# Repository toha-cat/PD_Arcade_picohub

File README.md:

# PD Arcade picohub
=================================

Firmware for Raspberry Pi Pico for use in Hatsune Miku Project DIVA Arcade Future Tone DIY-arcade controller 

Creates two USB-CDC and one HID devices:
- UART-bridge for connection [LKP](https://github.com/Project-Alpaca/LKP)-slider with [LKP-Serial](https://github.com/Project-Alpaca/LKP-FW) firmware.
- virtual COM-port that receives the commands for controlling the LEDs. Works in conjunction with the [PD-Arcade-Lights plugin](https://github.com/steelpuxnastik/PD-Arcade-Lights)
- HID-Gamepad for 5 buttons.

Example of PCB and it's description in [PCB folder](/PCB)

## Raspberry Pi Pico pin mapping
------------------------

| Raspberry Pi Pico GPIO | Function |
|-------------|-------------|
| 			**[LKP](https://github.com/Project-Alpaca/LKP)-slider connection**				|
| GPIO16 (Pin 21)        | UART0 TX |
| GPIO17 (Pin 22)        | UART0 RX |
| **LEDs**      |
| GPIO2 (Pin 4)          | BTN4  LED (Circle) |
| GPIO3 (Pin 5)          | BTN3  LED (Cross) |
| GPIO4 (Pin 6)          | BTN2  LED (Square) |
| GPIO5 (Pin 7)          | BTN1  LED (Triangle) |
| GPIO6 (Pin 9)          | R LINE B (RGB LED strip)|
| GPIO7 (Pin 10)         | R LINE R (RGB LED strip)|
| GPIO8 (Pin 11)         | R LINE G (RGB LED strip)|
| GPIO9 (Pin 12)         | L LINE B (RGB LED strip)|
| GPIO10 (Pin 14)        | L LINE R (RGB LED strip)|
| GPIO11 (Pin 15)        | L LINE G (RGB LED strip)|
| GPIO15 (Pin 20)        | LED-strip brightness PWM signal source|
| **Controls**	 			|
| GPIO18 (Pin 24)        |  BTN 1  (Triangle) |
| GPIO19 (Pin 25)        |  BTN 2  (Square) |
| GPIO20 (Pin 26)        |  BTN 3  (Cross) |
| GPIO21 (Pin 27)        |  BTN 4  (Circle) |
| GPIO22 (Pin 29)        |  BTN 5 (Start)  |

## Disclaimer
----------

This software is provided without warranty, according to the MIT License, and should therefore not be used where it may endanger life, financial stakes, or cause discomfort and inconvenience to others.

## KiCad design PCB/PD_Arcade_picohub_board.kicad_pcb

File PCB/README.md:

# PD Arcade picohub PCB
=================================

## Parts list
- PCB: 1x `PD_Arcade_picohub_board` **1.6mm thickness** (KiCad 7.99+ (7.99.0-697-g4d05bd62da), release build required for exporting Gerber files or take Gerber files archive in `PCB/gerber/PD_Arcade_picohub_board.zip`)
  - U1: `Raspberry Pi Pico` board
  - U2, U3: 2x `ULN2003` transistor assembly
  - U4: `TXS0108EPW` bi-directional level-shifter *(used for connection [SHINSANWASWITCH](https://github.com/steelpuxnastik/SHINSANWASWITCH) optical switches as main buttons and [LKP](https://github.com/Project-Alpaca/LKP) slider. Those components are basically uses 5v power supply, that is why it needs level shifter to connect to Raspberry Pi Pico that uses 3.3v signal level. There are possible other configurations of those components and in case of their 3.3v power supply you can exclude `TXS0108EPW` and connect them directly to Raspberry Pi Pico pins bypassing level shifter)*
  - C1, C2: `0.1uf` 0603 SMD condenser *(used for level shifter)*
- Parts for PWM brightness control (short jumpers if no PWM used, **brightness control will not work**):
  - Q1: `IRFR9024N` P-channel MOSFET
  - Q2: `AO3404A` N-channel MOSFET
  - R1: `1k` 1206 SMD resistor
  - R2: `10k` 1206 SMD resistor
- connectors:
  - 2x DIP-16 panel for `ULN2003`
  - 5x `JST XH-02` male connector
  - 4x `JST XH-03` male connector *(used for connection [SHINSANWASWITCH](https://github.com/steelpuxnastik/SHINSANWASWITCH) optical switches for main buttons. It's an active component, so it uses 3 wires. If you use passive switches - you can change to `JST XH-02` and connect it directly to Raspberry Pi Pico pins bypassing level shifter)*
  - 6x `JST XH-04` male connector
  - female 2.54 single row headset for `Raspberry Pi Pico`

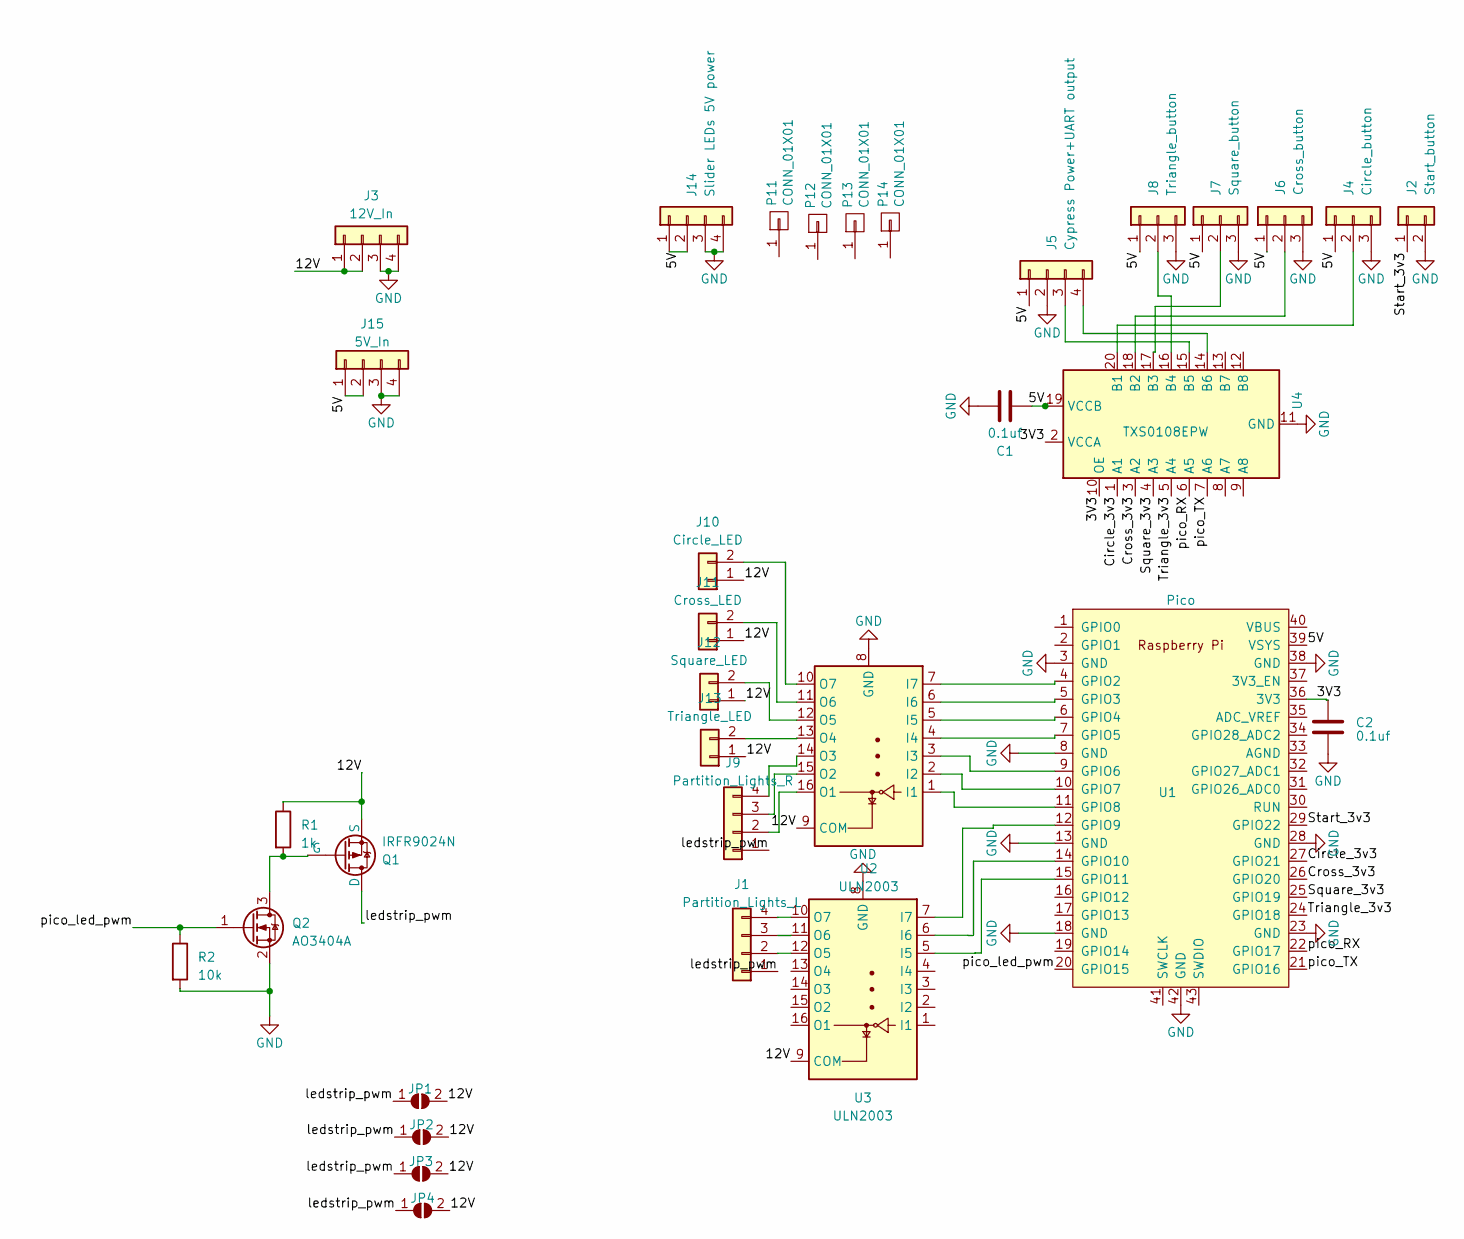
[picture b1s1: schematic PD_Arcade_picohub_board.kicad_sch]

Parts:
C1, C2: 0.1uf; C_0805_2012Metric
J1: Partition_Lights_L; JST_XH_B4B-XH-A_1x04_P2.50mm_Vertical
J2: Start_button; JST_XH_B2B-XH-A_1x02_P2.50mm_Vertical
J3: 12V_In; JST_XH_B4B-XH-A_1x04_P2.50mm_Vertical
J4: Circle_button; JST_XH_B3B-XH-A_1x03_P2.50mm_Vertical
J5: Cypress Power+UART output; JST_XH_B4B-XH-A_1x04_P2.50mm_Vertical
J6: Cross_button; JST_XH_B3B-XH-A_1x03_P2.50mm_Vertical
J7: Square_button; JST_XH_B3B-XH-A_1x03_P2.50mm_Vertical
J8: Triangle_button; JST_XH_B3B-XH-A_1x03_P2.50mm_Vertical
J9: Partition_Lights_R; JST_XH_B4B-XH-A_1x04_P2.50mm_Vertical
J10: Circle_LED; JST_XH_B2B-XH-A_1x02_P2.50mm_Vertical
J11: Cross_LED; JST_XH_B2B-XH-A_1x02_P2.50mm_Vertical
J12: Square_LED; JST_XH_B2B-XH-A_1x02_P2.50mm_Vertical
J13: Triangle_LED; JST_XH_B2B-XH-A_1x02_P2.50mm_Vertical
J14: Slider LEDs 5V power; JST_XH_B4B-XH-A_1x04_P2.50mm_Vertical
J15: 5V_In; JST_XH_B4B-XH-A_1x04_P2.50mm_Vertical
JP1, JP2, JP3, JP4: SolderJumper_2_Open; SolderJumper-2_P1.3mm_Open_RoundedPad1.0x1.5mm
P11, P12, P13, P14: CONN_01X01; MountingHole_3.2mm_M3_Pad
Q1: IRFR9024N; TO-252-2
Q2: AO3404A; SOT-23
R1: 1k; R_1206_3216Metric
R2: 10k; R_1206_3216Metric
U1: Pico; RPi_Pico_SMD_TH
U2, U3: ULN2003; DIP-16_W7.62mm
U4: TXS0108EPW; TSSOP-20_4.4x6.5mm_P0.65mm

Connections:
/3V3: C2.1, U1.36 (3V3), U4.2 (VCCA), U4.10 (OE)
/5V: C1.2, J4.1, J5.1, J6.1, J7.1, J8.1, J14.1, J14.2, J15.1, J15.2, U1.39 (VSYS), U4.19 (VCCB)
/12V: J3.1, J3.2, J10.1, J11.1, J12.1, J13.1, JP1.2 (B), JP2.2 (B), JP3.2 (B), JP4.2 (B), Q1.3 (S), R1.1, U2.9 (COM), U3.9 (COM)
/Circle_3v3: U1.27 (GPIO21), U4.1 (A1)
/Cross_3v3: U1.26 (GPIO20), U4.3 (A2)
/Square_3v3: U1.25 (GPIO19), U4.4 (A3)
/Start_3v3: J2.1, U1.29 (GPIO22)
/Triangle_3v3: U1.24 (GPIO18), U4.5 (A4)
/ledstrip_pwm: J1.1, J9.1, JP1.1 (A), JP2.1 (A), JP3.1 (A), JP4.1 (A), Q1.2 (D)
/pico_RX: U1.22 (GPIO17), U4.6 (A5)
/pico_TX: U1.21 (GPIO16), U4.7 (A6)
/pico_led_pwm: Q2.1 (G), R2.1, U1.20 (GPIO15)
GND: C1.1, C2.2, J2.2, J3.3, J3.4, J4.3, J5.2, J6.3, J7.3, J8.3, J14.3, J14.4, J15.3, J15.4, Q2.2 (S), R2.2, U1.3 (GND), U1.8 (GND), U1.13 (GND), U1.18 (GND), U1.23 (GND), U1.28 (GND), U1.38 (GND), U1.42 (GND), U2.8 (GND), U3.8 (GND), U4.11 (GND)
unnamed: J1.2, U3.12 (O5)
unnamed: J1.3, U3.11 (O6)
unnamed: J1.4, U3.10 (O7)
unnamed: J4.2, U4.20 (B1)
unnamed: J5.3, U4.15 (B5)
unnamed: J5.4, U4.14 (B6)
unnamed: J6.2, U4.18 (B2)
unnamed: J7.2, U4.17 (B3)
unnamed: J8.2, U4.16 (B4)
unnamed: J9.2, U2.16 (O1)
unnamed: J9.3, U2.15 (O2)
unnamed: J9.4, U2.14 (O3)
unnamed: J10.2, U2.10 (O7)
unnamed: J11.2, U2.11 (O6)
unnamed: J12.2, U2.12 (O5)
unnamed: J13.2, U2.13 (O4)
unnamed: Q1.1 (G), Q2.3 (D), R1.2
unnamed: U1.4 (GPIO2), U2.7 (I7)
unnamed: U1.5 (GPIO3), U2.6 (I6)
unnamed: U1.6 (GPIO4), U2.5 (I5)
unnamed: U1.7 (GPIO5), U2.4 (I4)
unnamed: U1.9 (GPIO6), U2.3 (I3)
unnamed: U1.10 (GPIO7), U2.2 (I2)
unnamed: U1.11 (GPIO8), U2.1 (I1)
unnamed: U1.12 (GPIO9), U3.7 (I7)
unnamed: U1.14 (GPIO10), U3.6 (I6)
unnamed: U1.15 (GPIO11), U3.5 (I5)

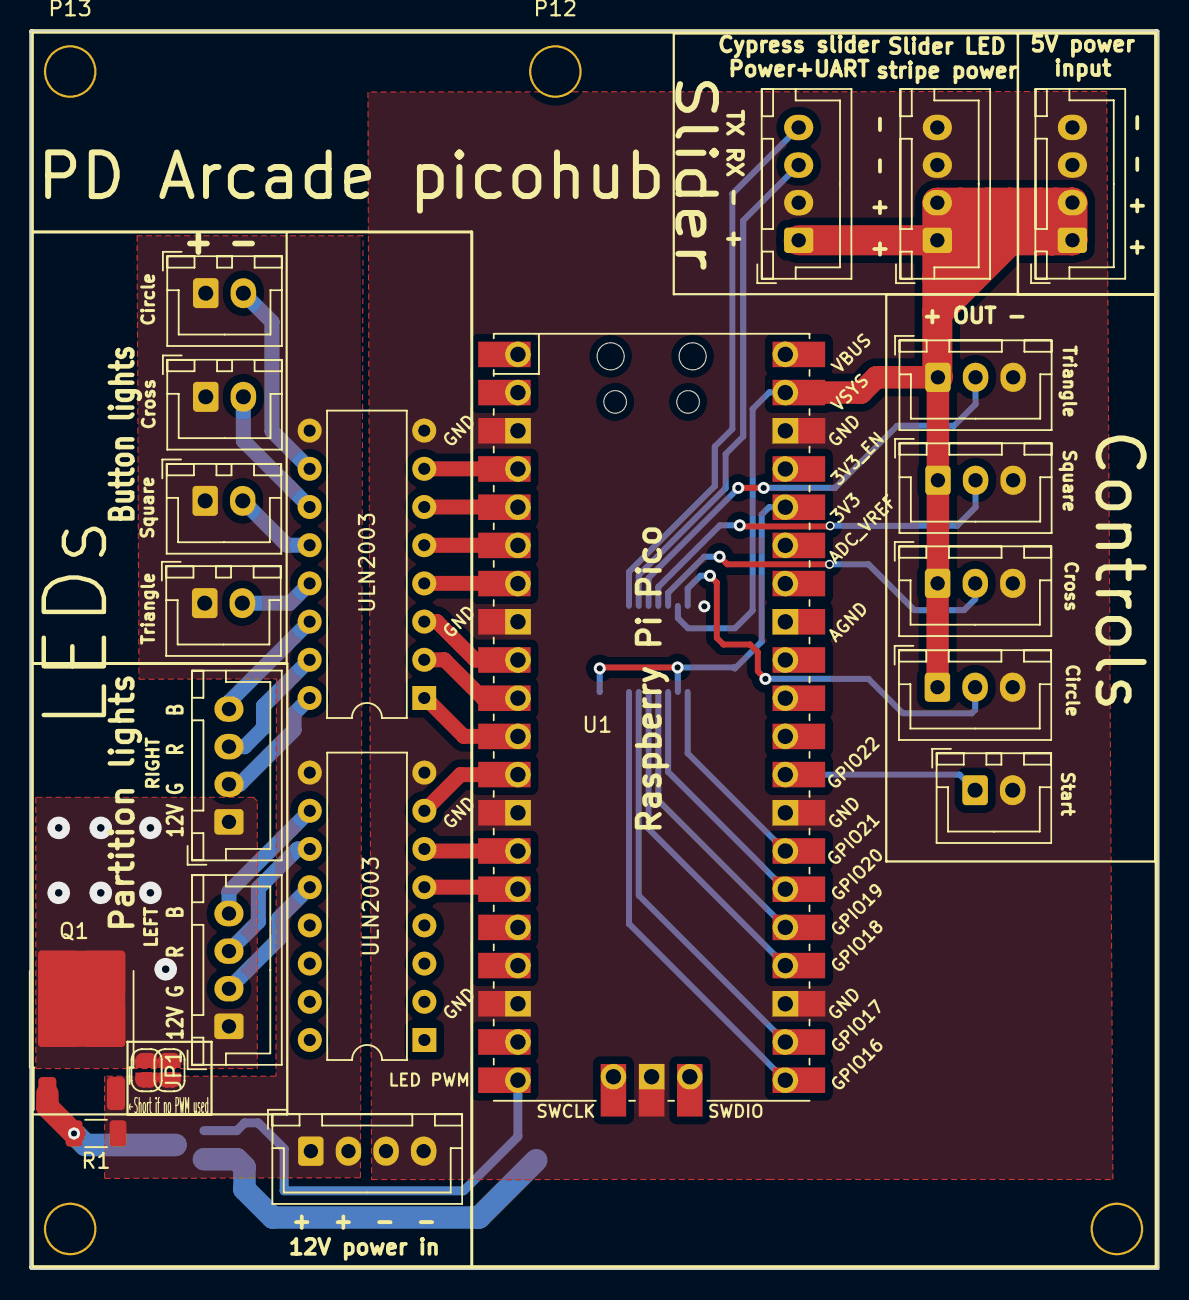
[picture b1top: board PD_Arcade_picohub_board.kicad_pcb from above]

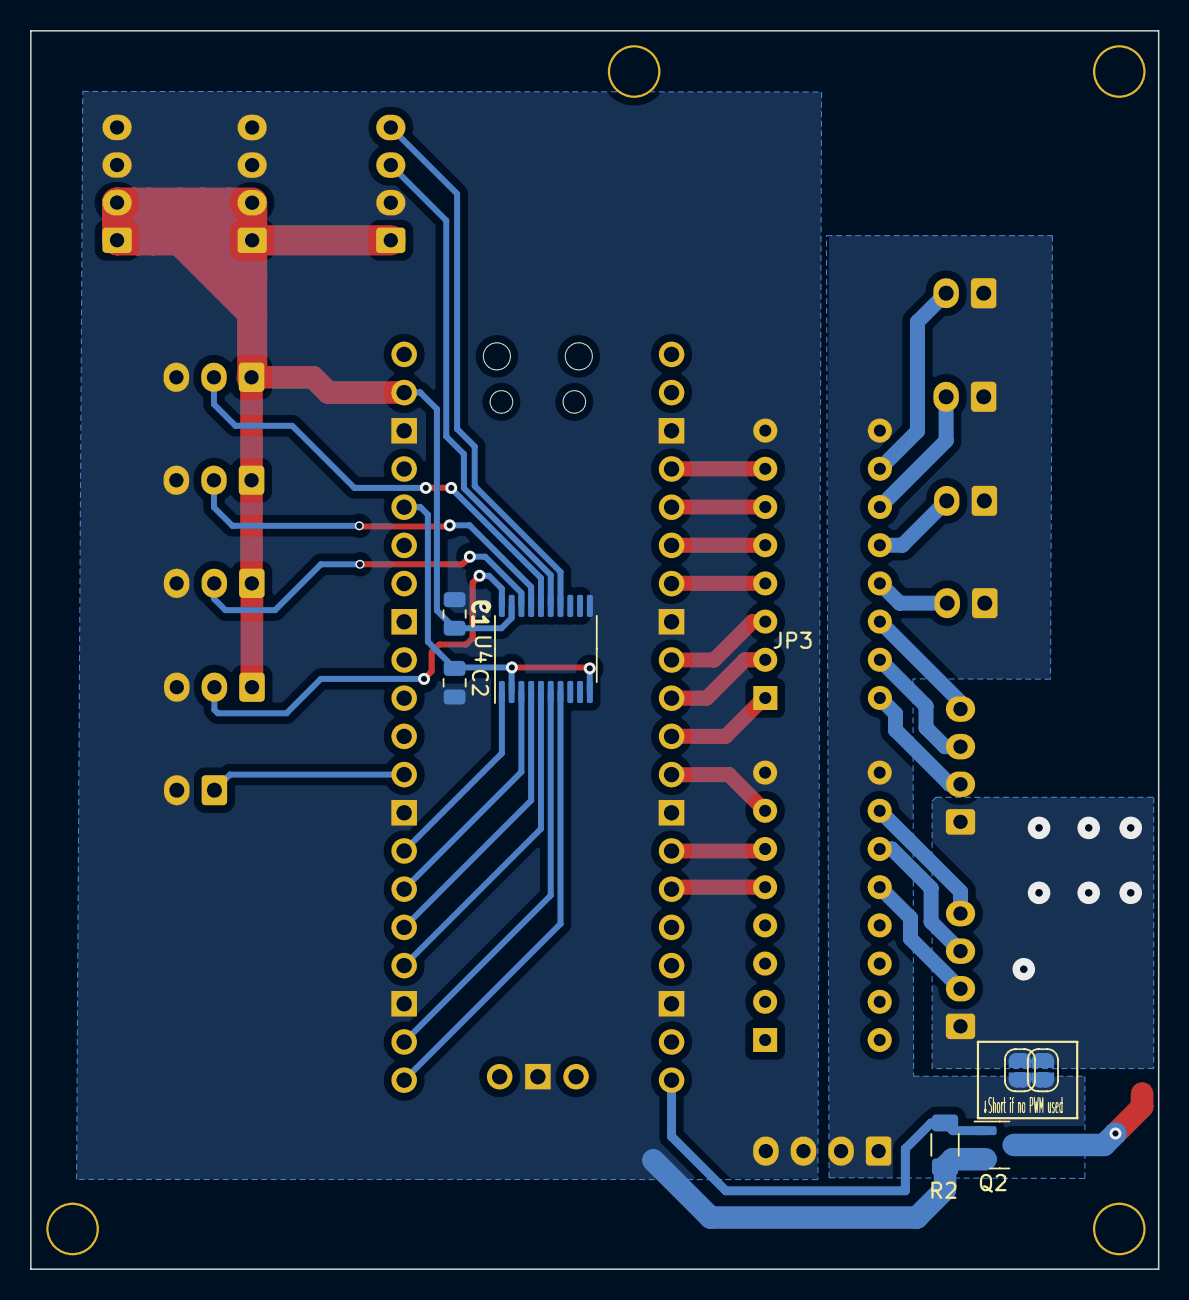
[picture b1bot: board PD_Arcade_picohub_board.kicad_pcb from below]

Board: 2 copper layers, 75.0 x 82.3 mm, 33 parts (7 on the bottom side), 40 nets.

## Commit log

2024-08-24 Init
2024-08-24 Add license and readmy
2024-08-24 fix readmy
2024-08-24 Fix pinout
2024-08-25 Change pins
2024-08-25 add generated files and sdk
2024-08-25 Fix getting led data. Code cleanup
2024-08-25 Set uart inst
2024-09-27 refactoring
2024-09-27 LED control protocol version 2
2024-09-27 Update link to plugin
2024-09-28 Add basic HID GamePad
2024-09-28 Add HID description
2024-09-30 Fix gamepad compatibility
2024-09-30 timer replacement
2024-10-21 Readme update
    a little more important details
2024-10-22 readme mistakes fix
2024-11-05 Update README.md
    According to the PCB
2024-11-06 addition PCB that used in project
2024-11-06 PCB readme
2024-11-06 Add set brightness ctl
2024-11-06 v.1.0
2024-11-07 README.md and PCB update
2024-11-08 README.md update
2024-11-25 R1 fix to 1k
    10k do not work
2024-11-25 assembled PCB
2024-12-10 change names of devices
